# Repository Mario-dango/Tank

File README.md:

This is the first time that I make a real project, I want to do my best on it and finish

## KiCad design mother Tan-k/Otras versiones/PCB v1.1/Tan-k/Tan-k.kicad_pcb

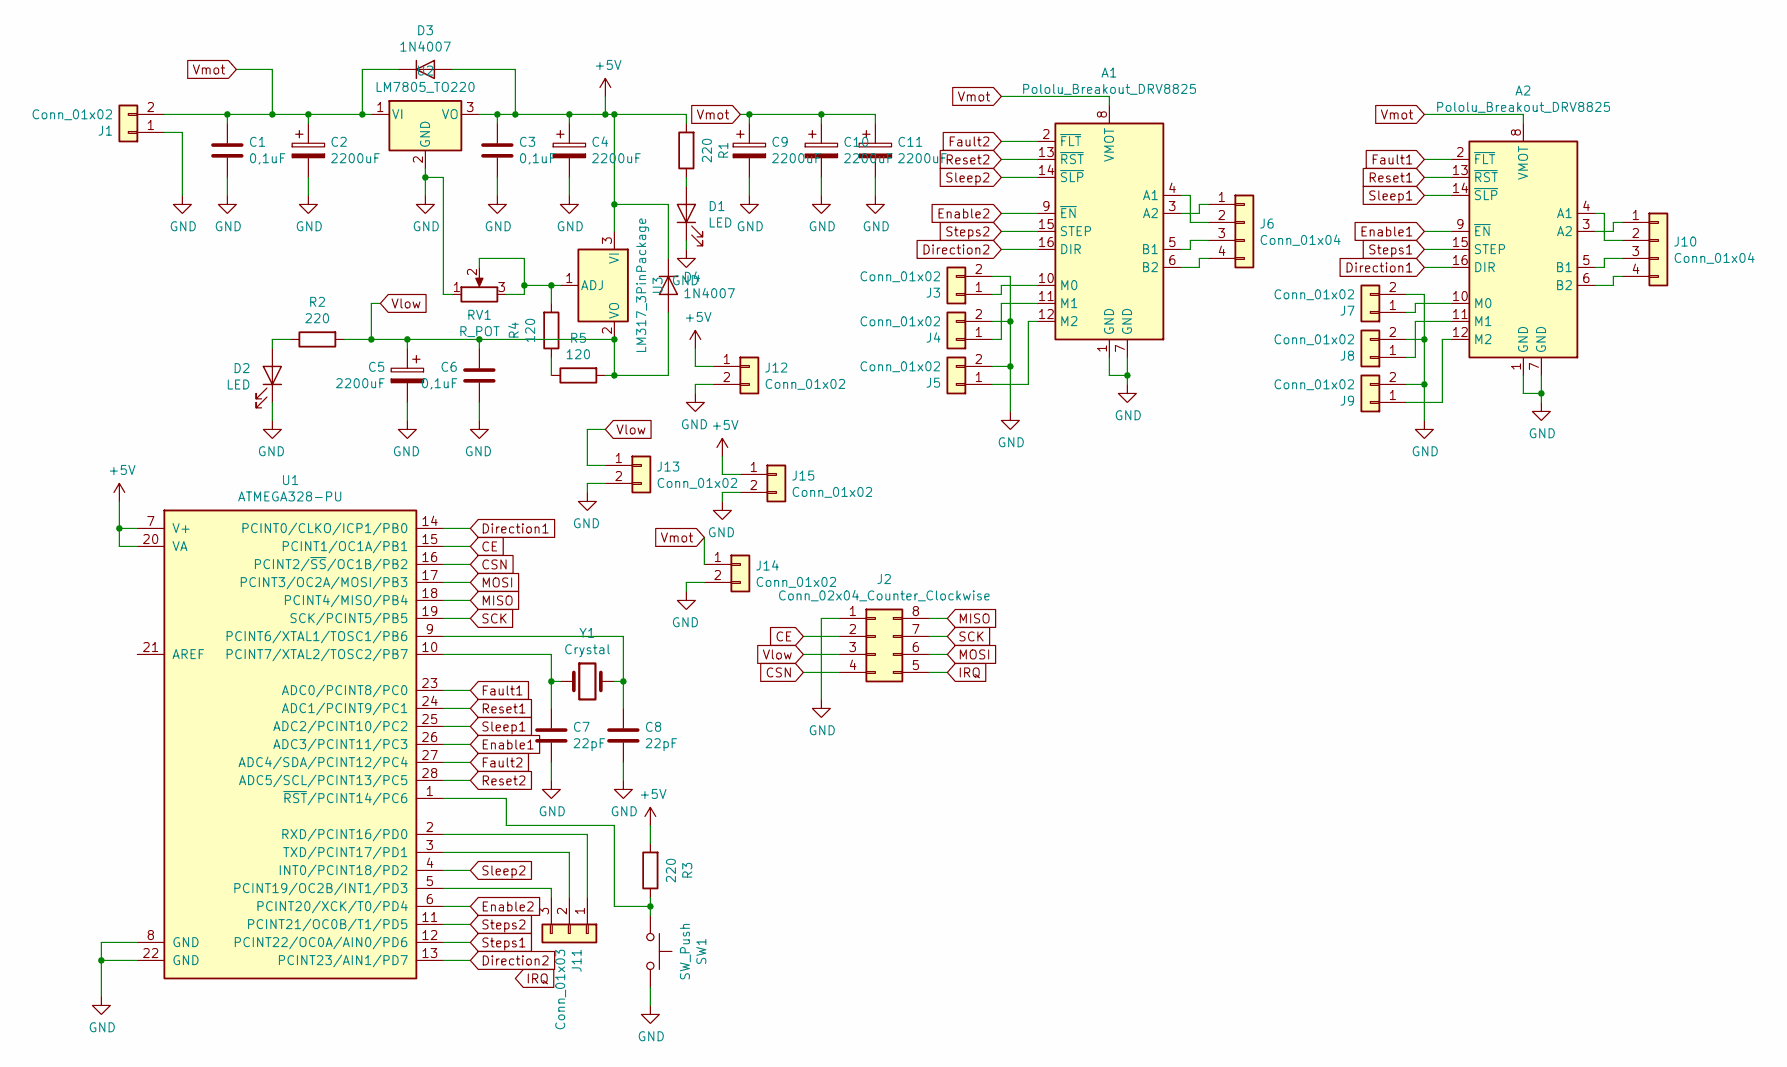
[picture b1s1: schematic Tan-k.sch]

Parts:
A1, A2: Pololu_Breakout_DRV8825; Pololu_Breakout-16_15.2x20.3mm
C1, C3, C6: 0,1uF; C_Disc_D5.0mm_W2.5mm_P5.00mm
C2, C5: 2200uF; CP_Radial_D10.0mm_P2.50mm_P5.00mm
C4, C9, C10, C11: 2200uF; CP_Radial_D13.0mm_P5.00mm
C7, C8: 22pF; C_Disc_D3.8mm_W2.6mm_P2.50mm
D1, D2: LED; LED_D5.0mm
D3, D4: 1N4007; D_DO-41_SOD81_P10.16mm_Horizontal
J1: Conn_01x02; PhoenixContact_MCV_1,5_2-G-5.08_1x02_P5.08mm_Vertical
J2: Conn_02x04_Counter_Clockwise; PinHeader_2x04_P2.54mm_Vertical
J3, J4, J5, J7, J8, J9, J12, J13, J14, J15: Conn_01x02; PinHeader_1x02_P2.54mm_Vertical
J6, J10: Conn_01x04; PinHeader_1x04_P2.54mm_Vertical
J11: Conn_01x03; PinHeader_1x03_P2.54mm_Vertical
R1, R2, R3: 220; R_Axial_DIN0207_L6.3mm_D2.5mm_P10.16mm_Horizontal
R4, R5: 120; R_Axial_DIN0207_L6.3mm_D2.5mm_P10.16mm_Horizontal
RV1: R_POT; Potentiometer_Bourns_3266X_Horizontal
SW1: SW_Push; SW_PUSH_6mm_H5mm
U1: ATMEGA328-PU; DIP-28_W7.62mm_Socket; MPN ATMEGA328-PU
U2: LM7805_TO220; TO-220-3_Vertical
U3: LM317_3PinPackage; TO-220-3_Vertical
Y1: Crystal; Crystal_HC52-6mm_Vertical

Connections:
+5V: C3.1, C4.1, D3.2 (A), D4.1 (K), J12.1, J15.1, R1.2, R3.2, U1.7 (V+), U1.20 (VA), U2.3 (VO), U3.3 (VI)
CE: J2.2, U1.15 (PCINT1/OC1A/PB1)
CSN: J2.4, U1.16 (PCINT2/~SS~/OC1B/PB2)
Direction1: A2.16 (DIR), U1.14 (PCINT0/CLKO/ICP1/PB0)
Direction2: A1.16 (DIR), U1.13 (PCINT23/AIN1/PD7)
Enable1: A2.9 (~EN), U1.26 (ADC3/PCINT11/PC3)
Enable2: A1.9 (~EN), U1.6 (PCINT20/XCK/T0/PD4)
Fault1: A2.2 (~FLT), U1.23 (ADC0/PCINT8/PC0)
Fault2: A1.2 (~FLT), U1.27 (ADC4/SDA/PCINT12/PC4)
GND: A1.1 (GND), A1.7 (GND), A2.1 (GND), A2.7 (GND), C1.2, C2.2, C3.2, C4.2, C5.2, C6.2, C7.2, C8.2, C9.2, C10.2, C11.2, D1.1 (K), D2.1 (K), J1.1, J2.1, J3.2, J4.2, J5.2, J7.2, J8.2, J9.2, J12.2, J13.2, J14.2, J15.2, RV1.1, SW1.1, U1.8 (GND), U1.22 (GND), U2.2 (GND)
IRQ: J2.5
MISO: J2.8, U1.18 (PCINT4/MISO/PB4)
MOSI: J2.6, U1.17 (PCINT3/OC2A/MOSI/PB3)
unnamed: A1.3 (A2), J6.1
unnamed: A1.4 (A1), J6.2
unnamed: A1.5 (B1), J6.3
unnamed: A1.6 (B2), J6.4
unnamed: A1.10 (M0), J3.1
unnamed: A1.11 (M1), J4.1
unnamed: A1.12 (M2), J5.1
unnamed: A2.3 (A2), J10.1
unnamed: A2.4 (A1), J10.2
unnamed: A2.5 (B1), J10.3
unnamed: A2.6 (B2), J10.4
unnamed: A2.10 (M0), J7.1
unnamed: A2.11 (M1), J8.1
unnamed: A2.12 (M2), J9.1
unnamed: C7.1, U1.10 (PCINT7/XTAL2/TOSC2/PB7), Y1.1
unnamed: C8.1, U1.9 (PCINT6/XTAL1/TOSC1/PB6), Y1.2
unnamed: D1.2 (A), R1.1
unnamed: D2.2 (A), R2.1
unnamed: J11.1, U1.2 (RXD/PCINT16/PD0)
unnamed: J11.2, U1.3 (TXD/PCINT17/PD1)
unnamed: J11.3, U1.5 (PCINT19/OC2B/INT1/PD3)
unnamed: R3.1, SW1.2, U1.1 (~RST~/PCINT14/PC6)
unnamed: R4.1, R5.1
unnamed: R4.2, RV1.2, RV1.3, U3.1 (ADJ)
Reset1: A2.13 (~RST), U1.24 (ADC1/PCINT9/PC1)
Reset2: A1.13 (~RST), U1.28 (ADC5/SCL/PCINT13/PC5)
SCK: J2.7, U1.19 (SCK/PCINT5/PB5)
Sleep1: A2.14 (~SLP), U1.25 (ADC2/PCINT10/PC2)
Sleep2: A1.14 (~SLP), U1.4 (INT0/PCINT18/PD2)
Steps1: A2.15 (STEP), U1.12 (PCINT22/OC0A/AIN0/PD6)
Steps2: A1.15 (STEP), U1.11 (PCINT21/OC0B/T1/PD5)
Vlow: C5.1, C6.1, D4.2 (A), J2.3, J13.1, R2.2, R5.2, U3.2 (VO)
Vmot: A1.8 (VMOT), A2.8 (VMOT), C1.1, C2.1, C9.1, C10.1, C11.1, D3.1 (K), J1.2, J14.1, U2.1 (VI)

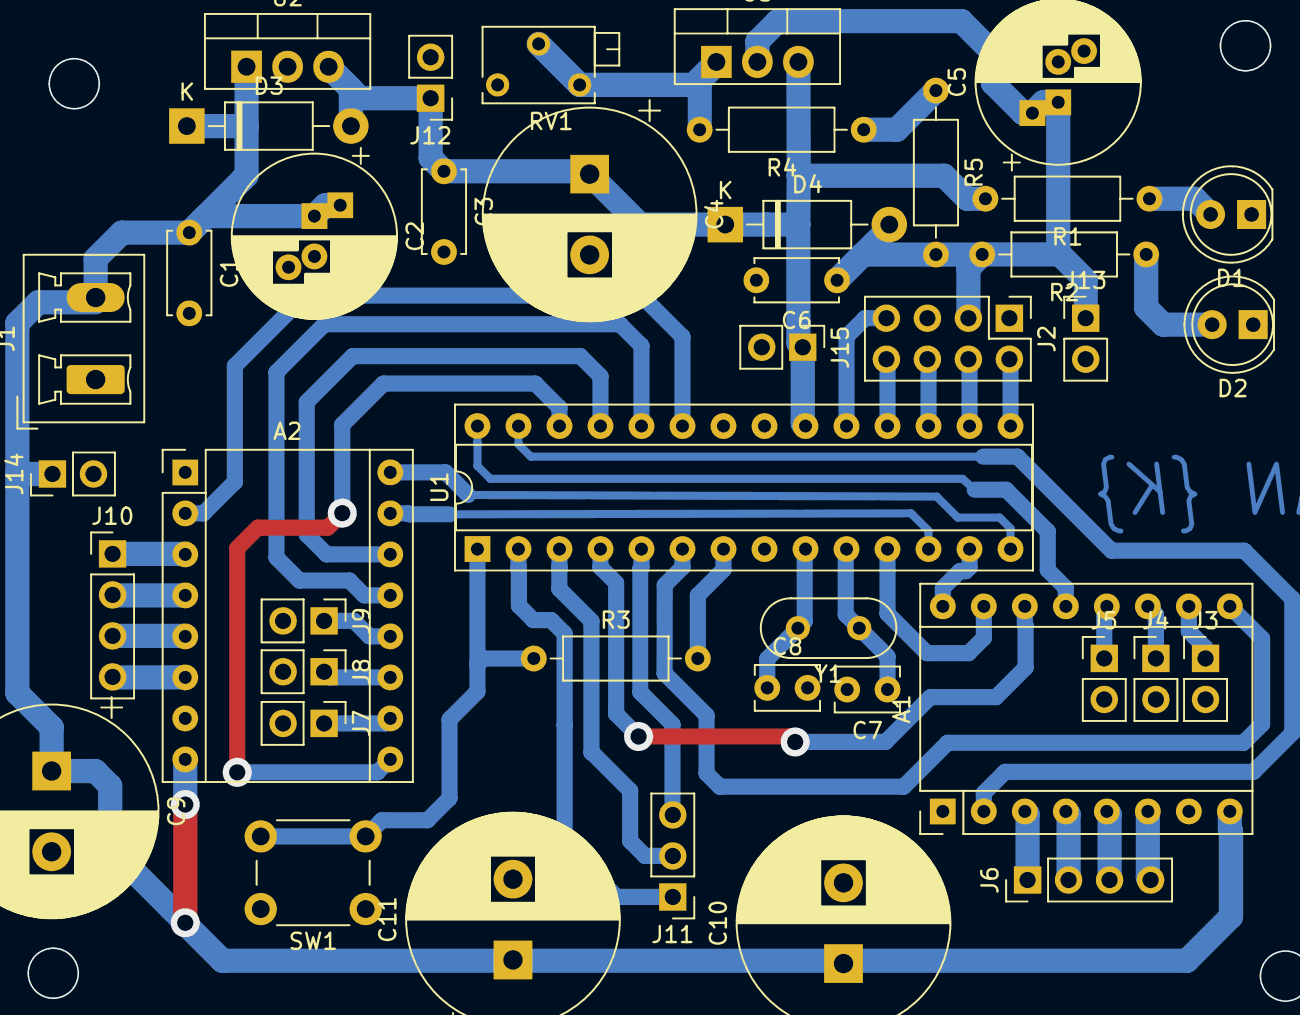
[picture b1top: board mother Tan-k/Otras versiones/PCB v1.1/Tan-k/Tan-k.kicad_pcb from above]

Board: 2 copper layers, 43 parts (0 on the bottom side), 45 nets.

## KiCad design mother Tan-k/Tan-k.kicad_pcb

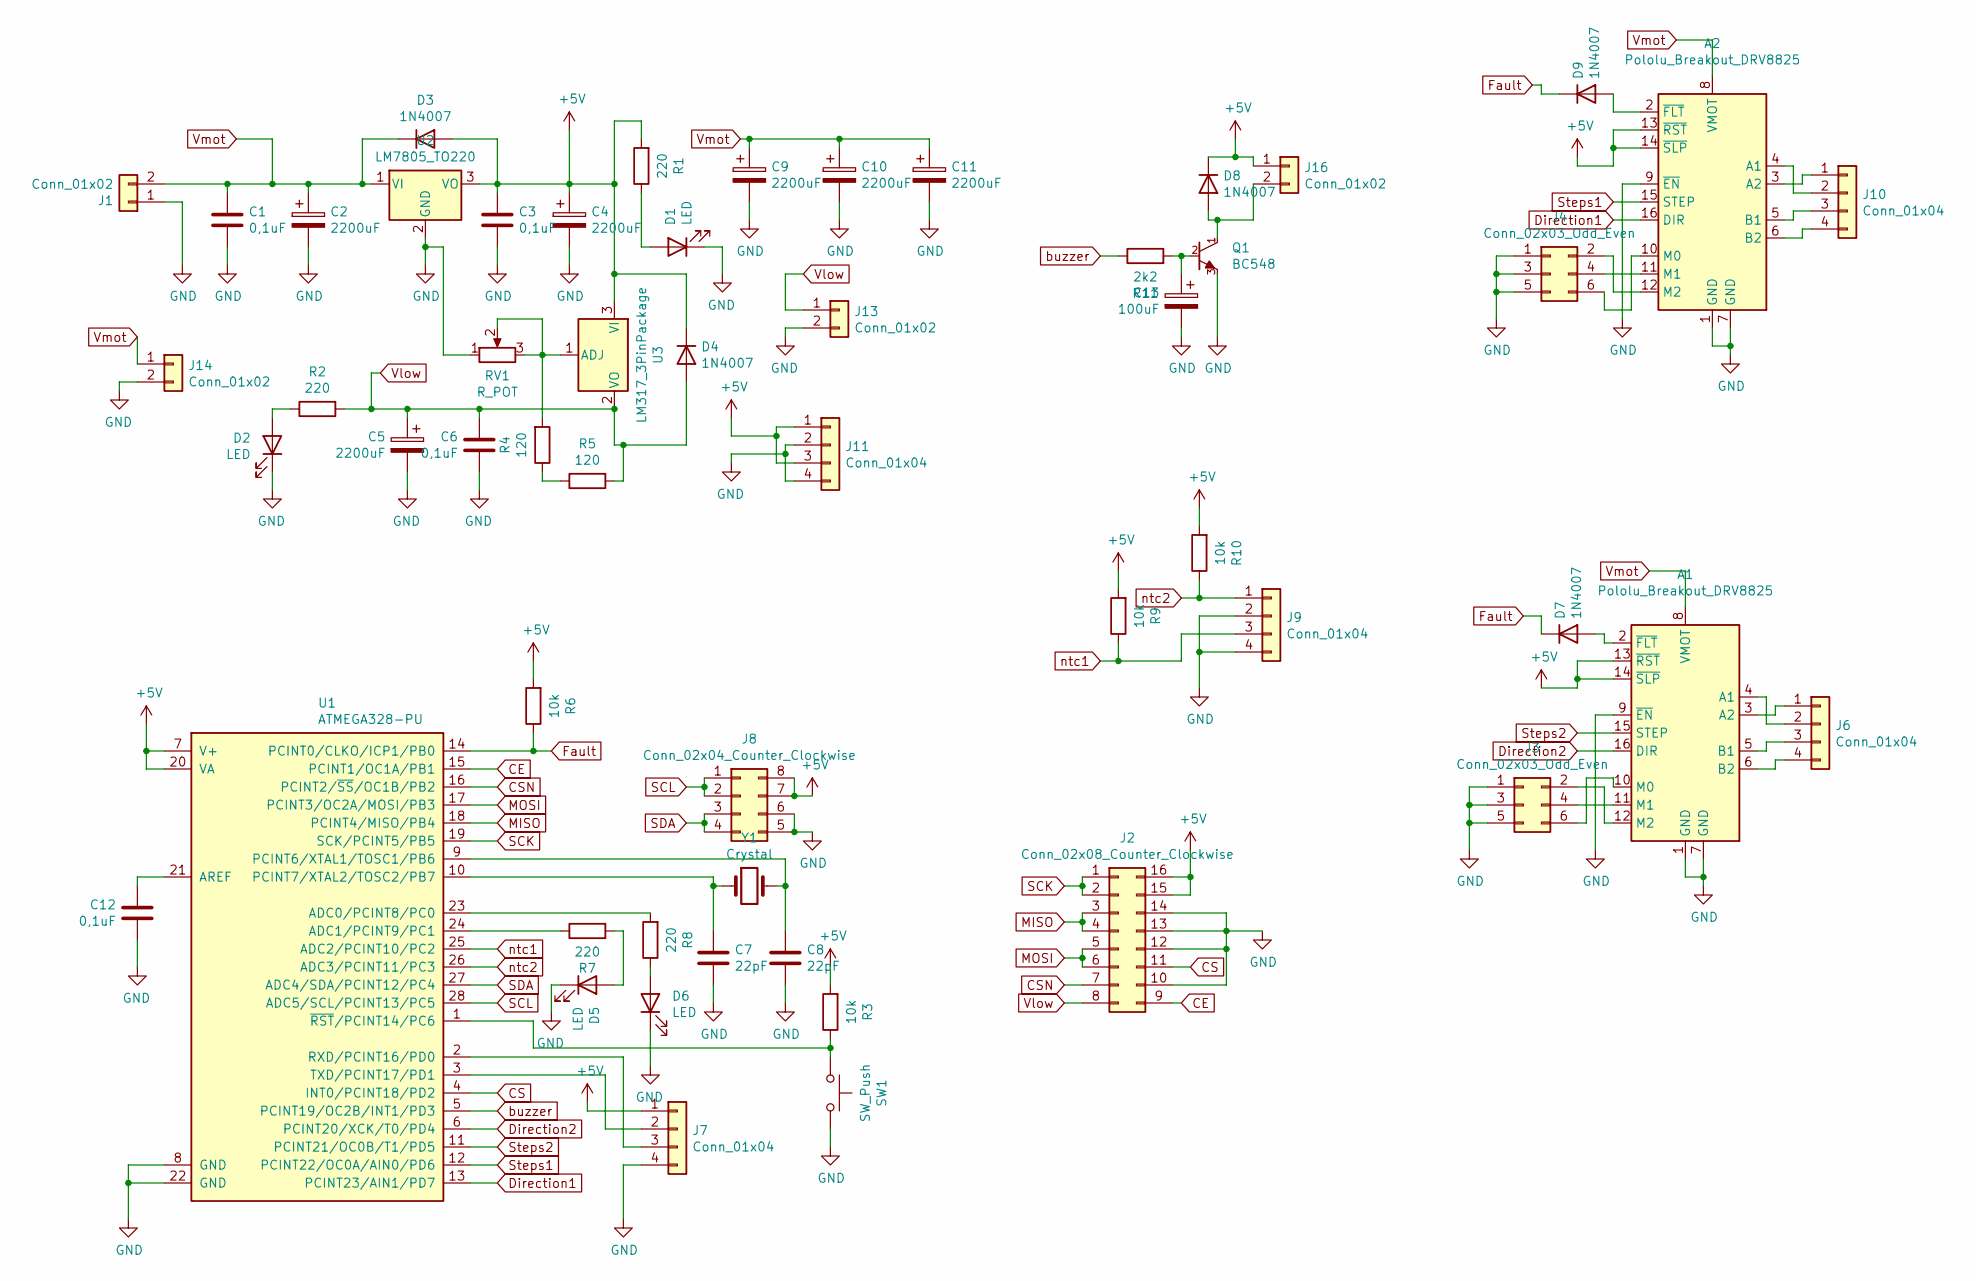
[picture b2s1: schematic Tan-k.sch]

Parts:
A1, A2: Pololu_Breakout_DRV8825; Pololu_Breakout-16_15.2x20.3mm
C1, C3, C6, C12: 0,1uF; C_Disc_D5.0mm_W2.5mm_P5.00mm
C2, C5: 2200uF; CP_Radial_D10.0mm_P2.50mm_P5.00mm
C4, C9, C10, C11: 2200uF; CP_Radial_D13.0mm_P5.00mm
C7, C8: 22pF; C_Disc_D3.8mm_W2.6mm_P2.50mm
C13: 100uF; CP_Radial_D5.0mm_P2.50mm
D1, D2, D5, D6: LED; LED_D5.0mm
D3, D4, D7, D8, D9: 1N4007; D_DO-41_SOD81_P10.16mm_Horizontal
J1: Conn_01x02; PhoenixContact_MCV_1,5_2-G-5.08_1x02_P5.08mm_Vertical
J2: Conn_02x08_Counter_Clockwise; PinHeader_2x08_P2.54mm_Vertical
J3, J4: Conn_02x03_Odd_Even; PinHeader_2x03_P2.54mm_Vertical
J6, J7, J9, J10, J11: Conn_01x04; PinHeader_1x04_P2.54mm_Vertical
J8: Conn_02x04_Counter_Clockwise; PinHeader_2x04_P2.54mm_Vertical
J13, J14, J16: Conn_01x02; PinHeader_1x02_P2.54mm_Vertical
Q1: BC548; TO-92_Wide
R1, R2, R7, R8: 220; R_Axial_DIN0207_L6.3mm_D2.5mm_P10.16mm_Horizontal
R3, R6, R9, R10: 10k; R_Axial_DIN0207_L6.3mm_D2.5mm_P10.16mm_Horizontal
R4, R5: 120; R_Axial_DIN0207_L6.3mm_D2.5mm_P10.16mm_Horizontal
R11: 2k2; R_Axial_DIN0207_L6.3mm_D2.5mm_P10.16mm_Horizontal
RV1: R_POT; Potentiometer_Bourns_3266X_Horizontal
SW1: SW_Push; SW_PUSH_6mm_H5mm
U1: ATMEGA328-PU; DIP-28_W7.62mm_Socket; MPN ATMEGA328-PU
U2: LM7805_TO220; TO-220-3_Vertical
U3: LM317_3PinPackage; TO-220-3_Vertical
Y1: Crystal; Crystal_HC49-U_Vertical

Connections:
+5V: A1.13 (~RST), A1.14 (~SLP), A2.13 (~RST), A2.14 (~SLP), C3.1, C4.1, D3.2 (A), D4.1 (K), D8.1 (K), J2.15, J2.16, J7.1, J8.7, J8.8, J11.1, J11.3, J16.1, R1.2, R3.2, R6.2, R9.2, R10.2, U1.7 (V+), U1.20 (VA), U2.3 (VO), U3.3 (VI)
CE: J2.9, U1.15 (PCINT1/OC1A/PB1)
CS: J2.11, U1.4 (INT0/PCINT18/PD2)
CSN: J2.7, U1.16 (PCINT2/~SS~/OC1B/PB2)
Direction1: A2.16 (DIR), U1.13 (PCINT23/AIN1/PD7)
Direction2: A1.16 (DIR), U1.6 (PCINT20/XCK/T0/PD4)
Fault: D7.1 (K), D9.1 (K), R6.1, U1.14 (PCINT0/CLKO/ICP1/PB0)
GND: A1.1 (GND), A1.7 (GND), A1.9 (~EN), A2.1 (GND), A2.7 (GND), A2.9 (~EN), C1.2, C2.2, C3.2, C4.2, C5.2, C6.2, C7.2, C8.2, C9.2, C10.2, C11.2, C12.2, C13.2, D1.1 (K), D2.1 (K), D5.1 (K), D6.1 (K), J1.1, J2.10, J2.12, J2.13, J2.14, J3.1, J3.3, J3.5, J4.1, J4.3, J4.5, J7.4, J8.5, J8.6, J9.2, J9.4, J11.2, J11.4, J13.2, J14.2, Q1.3 (E), RV1.1, SW1.1, U1.8 (GND), U1.22 (GND), U2.2 (GND)
MISO: J2.3, J2.4, U1.18 (PCINT4/MISO/PB4)
MOSI: J2.5, J2.6, U1.17 (PCINT3/OC2A/MOSI/PB3)
unnamed: A1.2 (~FLT), D7.2 (A)
unnamed: A1.3 (A2), J6.1
unnamed: A1.4 (A1), J6.2
unnamed: A1.5 (B1), J6.3
unnamed: A1.6 (B2), J6.4
unnamed: A1.10 (M0), J3.6
unnamed: A1.11 (M1), J3.4
unnamed: A1.12 (M2), J3.2
unnamed: A2.2 (~FLT), D9.2 (A)
unnamed: A2.3 (A2), J10.1
unnamed: A2.4 (A1), J10.2
unnamed: A2.5 (B1), J10.3
unnamed: A2.6 (B2), J10.4
unnamed: A2.10 (M0), J4.6
unnamed: A2.11 (M1), J4.4
unnamed: A2.12 (M2), J4.2
unnamed: C7.1, U1.10 (PCINT7/XTAL2/TOSC2/PB7), Y1.1
unnamed: C8.1, U1.9 (PCINT6/XTAL1/TOSC1/PB6), Y1.2
unnamed: C12.1, U1.21 (AREF)
unnamed: C13.1, Q1.2 (B), R11.2
unnamed: D1.2 (A), R1.1
unnamed: D2.2 (A), R2.1
unnamed: D5.2 (A), R7.2
unnamed: D6.2 (A), R8.1
unnamed: D8.2 (A), J16.2, Q1.1 (C)
unnamed: J7.2, U1.3 (TXD/PCINT17/PD1)
unnamed: J7.3, U1.2 (RXD/PCINT16/PD0)
unnamed: R3.1, SW1.2, U1.1 (~RST~/PCINT14/PC6)
unnamed: R4.1, R5.1
unnamed: R4.2, RV1.2, RV1.3, U3.1 (ADJ)
unnamed: R7.1, U1.24 (ADC1/PCINT9/PC1)
unnamed: R8.2, U1.23 (ADC0/PCINT8/PC0)
SCK: J2.1, J2.2, U1.19 (SCK/PCINT5/PB5)
SCL: J8.1, J8.2, U1.28 (ADC5/SCL/PCINT13/PC5)
SDA: J8.3, J8.4, U1.27 (ADC4/SDA/PCINT12/PC4)
Steps1: A2.15 (STEP), U1.12 (PCINT22/OC0A/AIN0/PD6)
Steps2: A1.15 (STEP), U1.11 (PCINT21/OC0B/T1/PD5)
Vlow: C5.1, C6.1, D4.2 (A), J2.8, J13.1, R2.2, R5.2, U3.2 (VO)
Vmot: A1.8 (VMOT), A2.8 (VMOT), C1.1, C2.1, C9.1, C10.1, C11.1, D3.1 (K), J1.2, J14.1, U2.1 (VI)
buzzer: R11.1, U1.5 (PCINT19/OC2B/INT1/PD3)
ntc1: J9.3, R9.1, U1.25 (ADC2/PCINT10/PC2)
ntc2: J9.1, R10.1, U1.26 (ADC3/PCINT11/PC3)

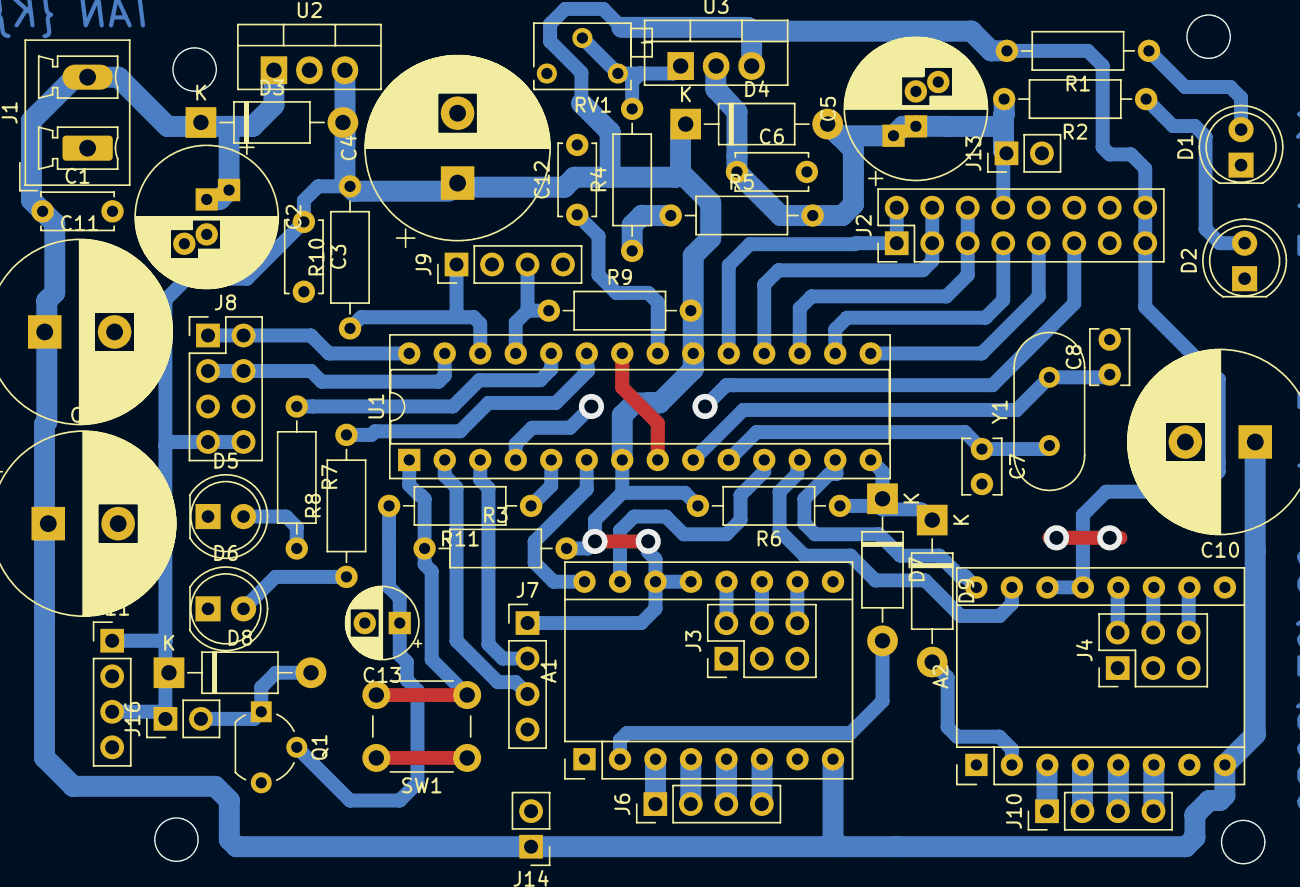
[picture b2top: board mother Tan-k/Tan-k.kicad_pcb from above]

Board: 2 copper layers, 55 parts (0 on the bottom side), 52 nets.

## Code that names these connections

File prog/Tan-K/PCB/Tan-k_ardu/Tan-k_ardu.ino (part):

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#define Fault 8 //Entrada por si hay algún problema con los DRV8825

//Etiquetas definidas para el uso general de pines
#define NTC1 A2  //Entrada para sensar temperaturas o alguna LDR
#define NTC2 A3  //Entrada para sensar temperaturas o alguna LDR
#define temp_r 10000  //Resistencia en serie con el termistor para divisor de tensión
#define LedALR A1 //Salida led indicadora de que hay un problema
#define LedOKA A0 //Salida led indicadora de que está todo OKAY
//#define buzzer 9 //Salida del Parlante indicador
//const int speakerPin = 9;

//Cosntantes de nivel, para velocidades de pulsos para los motores
const int velMax = 1000;
const int cteVel = 200;
// variable para almacenar la temperatura y resistencia
float temp1 = 0;    //Temperatura correspondiente al termistor en NTC1
uint32_t res1 = 0;  //Resistencia actual correspondiente al termistor en NTC1
float temp2 = 0;    //Temperatura correspondiente al termistor en NTC2
uint32_t res2 = 0;  //Resistencia actual correspondiente al termistor en NTC2

//Creo los objetos motor Izquierdo y motor Derecho para posterior uso
AccelStepper motorIZQ = AccelStepper(DRV8825, pulsosIZQ, dirIZQ); //Creamos la instancia motor Izquierdo
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
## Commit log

2021-11-19 modificación readme.md
